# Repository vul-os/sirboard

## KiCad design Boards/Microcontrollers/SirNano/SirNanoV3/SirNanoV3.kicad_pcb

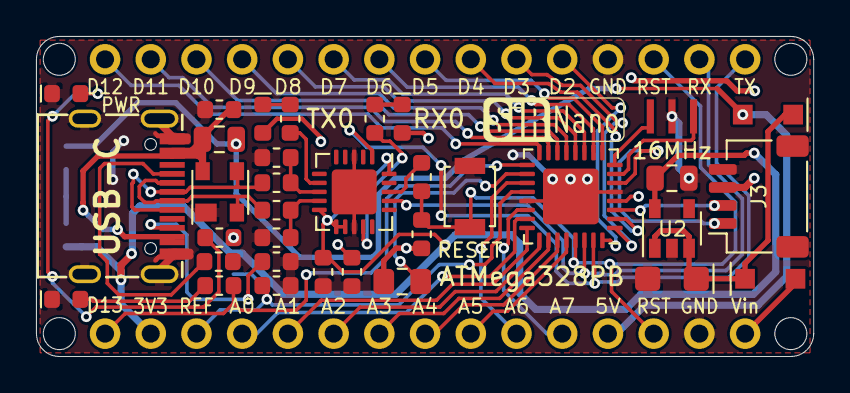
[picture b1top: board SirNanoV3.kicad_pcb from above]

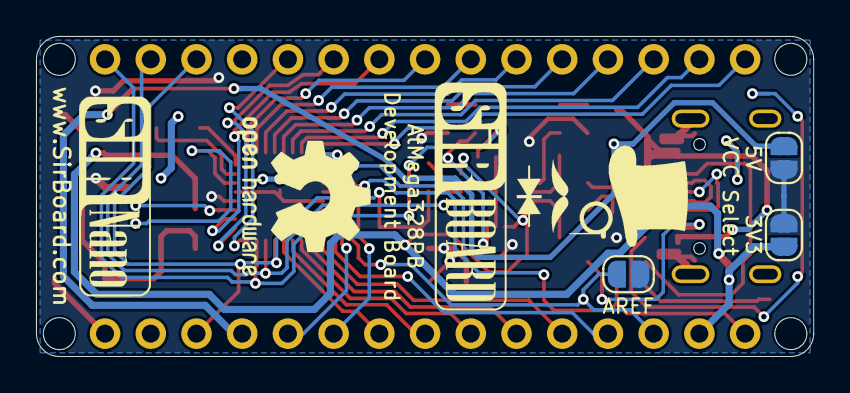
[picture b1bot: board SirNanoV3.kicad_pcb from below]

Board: 2 copper layers, 43.2 x 17.8 mm, 43 parts (5 on the bottom side), 49 nets.

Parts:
C1, C3, C9, C11: 100nF; C_0603_1608Metric
C2, C4: 47pF; C_0603_1608Metric
C6: 10nF; C_0603_1608Metric
C7: 10uF; C_0805_2012Metric
C8: 22uF; CP_EIA-3216-12_Kemet-S
D1: PRTR5V0U2X; SOT-143
D2, D3: MBR120; D_SOD-123F
D13: LED; LED_0603_1608Metric
F1: 500mA; R_0805_2012Metric
H1, H2, H3, H4: MountingHole; MountingHole_2.2mm_M2
J1, J2: Conn_01x15; PinHeader_1x15_P2.54mm_Vertical
J3: SirBlue; SirBlue_Connector
JP1, JP2, JP3: AREF; SolderJumper-2_P1.3mm_Open_RoundedPad1.0x1.5mm
L1: 10uH; L_0805_2012Metric_Pad1.15x1.40mm_HandSolder
PWR: LED; LED_0603_1608Metric
R1, R2: 27e; R_0603_1608Metric
R3: 10k; R_0603_1608Metric
R4, R8, R9, R10: 1k; R_0603_1608Metric
R11, R12: 5K1; R_0603_1608Metric
RESET: SW_Push; SW_SPST_B3U-1000P
RX0: LED; LED_0603_1608Metric
TX0: LED; LED_0603_1608Metric
U1: ATmega328PB-MU; QFN-32-1EP_5x5mm_P0.5mm_EP3.1x3.1mm
U2: SPX3819M5-L-3-3; SOT-23-5
U3: FT231XQ; QFN-20-1EP_4x4mm_P0.5mm_EP2.5x2.5mm
USB-C: USB_C_Plug_USB2.0; USB_C
Y1: 16MHz; Resonator_SMD_muRata_CSTxExxV-3Pin_3.0x1.1mm

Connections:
3V3: C3.1, C7.1, J2.14, JP3.1, U2.5, U3.10, U3.11, U3.12, U3.20
/D13LED: D13.2, R9.2
/LDO_in: C8.1, D2.1, D3.1, U2.1, U2.3
/PWRLED: PWR.2, R10.2
/RXLED: R4.2, RX0.1
/TXLED: R8.2, TX0.1
/X1: U1.7, Y1.3
/X2: U1.8, Y1.1
/uD+: C2.1, R1.2, U3.8
/uD-: C4.1, R2.2, U3.9
A0: J2.12, U1.23
A1: J2.11, U1.24
A2: J2.10, U1.25
A3: J2.9, U1.26
A4: J2.8, U1.27
A5: J2.7, U1.28
A6: J2.6, U1.19
A7: J2.5, U1.22
AREF: C1.1, J2.13, JP1.1, U1.20
D2: J1.11, U1.32
D3: J1.10, U1.1
D4: J1.9, U1.2
D5: J1.8, U1.9
D6: J1.7, U1.10
D7: J1.6, U1.11
D8: J1.5, U1.12
D9: J1.4, U1.13
D10: J1.3, U1.14
D11: J1.2, U1.15
D12: J1.1, U1.16
D13: J2.15, R9.1, U1.17
D+: D1.3, R1.1, USB-C.A6, USB-C.B6
D-: D1.2, R2.1, USB-C.A7, USB-C.B7
GND: C1.2, C2.2, C3.2, C4.2, C6.2, C7.2, C8.2, C9.2, D1.1, D13.1, J1.12, J2.2, J3.4, PWR.1, R11.1, R12.1, RESET.2, U1.5, U1.21, U1.33, U2.2, U3.3, U3.13, U3.21, USB-C.A1, USB-C.A12, USB-C.B1, USB-C.B12, USB-C.S1, Y1.2
unnamed: C11.2, U3.18
unnamed: L1.2, U1.18
unnamed: R12.2, USB-C.A5
unnamed: R11.2, USB-C.B5
RESET: C11.1, J1.13, J2.3, R3.2, RESET.1, U1.29
RX: J1.14, U1.30, U3.17
RX_LED: R4.1, U3.14
SCL1: J3.1, U1.6
SDA1: J3.2, U1.3
TX: J1.15, U1.31, U3.1
TX_LED: R8.1, U3.7
VBUS: C6.1, D1.4, F1.2, USB-C.A4, USB-C.A9, USB-C.B4, USB-C.B9
VCC: C9.1, J3.3, JP1.2, JP2.2, JP3.2, L1.1, R3.1, R10.1, RX0.2, TX0.2, U1.4
VIN: D3.2, J2.1
VUSB: D2.2, F1.1, J2.4, JP2.1

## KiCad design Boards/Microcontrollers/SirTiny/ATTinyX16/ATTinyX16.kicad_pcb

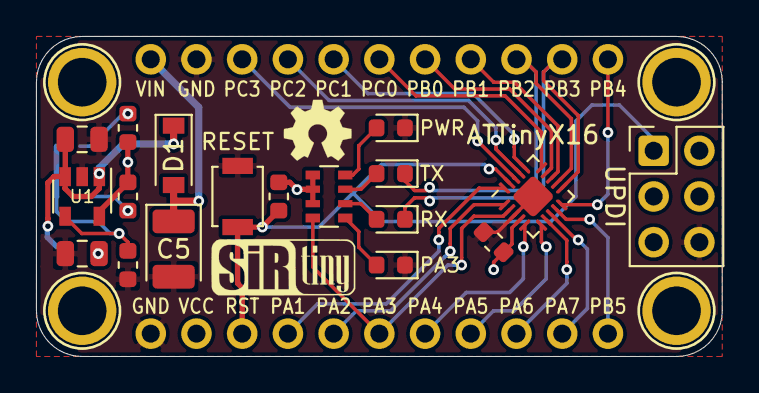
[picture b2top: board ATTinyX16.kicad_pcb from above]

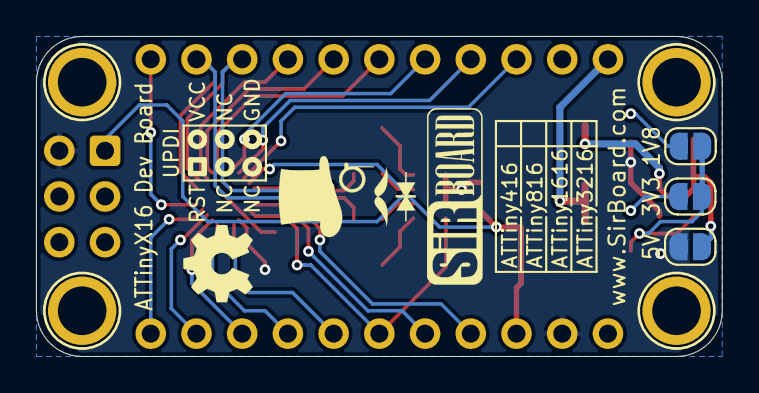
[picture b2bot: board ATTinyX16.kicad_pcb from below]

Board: 2 copper layers, 38.1 x 17.8 mm, 27 parts (5 on the bottom side), 29 nets.

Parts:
1V8, 3V3, 5V: SolderJumper_2_Open; SolderJumper-2_P1.3mm_Open_RoundedPad1.0x1.5mm
C1: 10uF; C_0805_2012Metric
C2: 2u2; C_0805_2012Metric
C3: 100nF; C_0603_1608Metric
C5: 22uF; CP_EIA-3528-15_AVX-H
D1: MBR120; D_SOD-123
H1, H2, H3, H4: MountingHole; MountingHole_M2.5_SirBoard
J1, J2: Conn_01x11; PinHeader_1x11_P2.54mm_Vertical
PA3: BLUE; LED_0603_1608Metric
PWR: RED; LED_0603_1608Metric
R3: 39k; R_0603_1608Metric
R4: 12.4k; R_0603_1608Metric
R5: 18k; R_0603_1608Metric
R6: 10k; R_0603_1608Metric
RESET: RST; SW_SPST_B3U-1000P
RN1: 330E; R_Array_Convex_4x0603
RX: YEL; LED_0603_1608Metric
TX: YEL; LED_0603_1608Metric
U1: AP7365; SOT-23-5
U2: ATtiny1616-M; VQFN-20-1EP_3x3mm_P0.4mm_EP1.7x1.7mm
UPDI: UPDI; PinHeader_2x03_P2.54mm_Vertical

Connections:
/1V8: 1V8.2, R5.2
/3V3: 3V3.2, R3.2
/ADJ: 1V8.1, 3V3.1, R4.1, U1.4
GND: C1.2, C2.2, C3.2, C5.2, J1.1, J2.2, PA3.1, PWR.1, R4.2, RESET.2, U1.2, U2.3, U2.21, UPDI.6
unnamed: 5V.2, C1.1, D1.1, U1.1, U1.3
unnamed: PA3.2, RN1.1
unnamed: PWR.2, RN1.4
unnamed: RN1.2, RX.2
unnamed: RN1.3, TX.2
PA1: J1.4, U2.20
PA2: J1.5, U2.1
PA3: J1.6, RN1.8, U2.2
PA4: J1.7, U2.5
PA5: J1.8, U2.6
PA6: J1.9, U2.7
PA7: J1.10, U2.8
PB0: J2.7, U2.14
PB1: J2.8, U2.13
PB4: J2.11, U2.10
PB5: J1.11, U2.9
PC0: J2.6, U2.15
PC1: J2.5, U2.16
PC2: J2.4, U2.17
PC3: J2.3, U2.18
RST: J1.3, R6.2, RESET.1, U2.19, UPDI.1
RXD: J2.10, RX.1, U2.11
TXD: J2.9, TX.1, U2.12
VCC: 5V.1, C2.1, C3.1, J1.2, R3.1, R5.1, R6.1, RN1.5, RN1.6, RN1.7, U1.5, U2.4, UPDI.2
VIN: C5.1, D1.2, J2.1

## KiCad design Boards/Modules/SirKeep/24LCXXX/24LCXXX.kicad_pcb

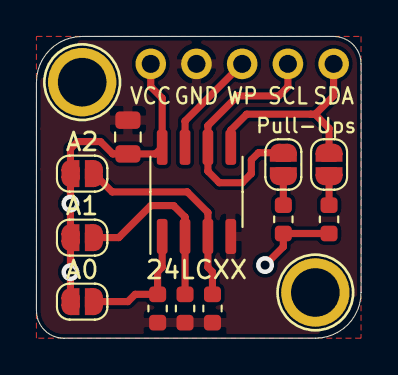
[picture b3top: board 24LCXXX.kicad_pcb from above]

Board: 2 copper layers, 18.0 x 16.8 mm, 15 parts (0 on the bottom side), 10 nets.

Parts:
24LCXX: 24LC1025; SOIC-8_3.9x4.9mm_P1.27mm
A0, A1, A2: SolderJumper_2_Open; SolderJumper-2_P1.3mm_Open_RoundedPad1.0x1.5mm
C1: 1uF; C_0805_2012Metric
H1, H2: MountingHole; MountingHole_M2.5_SirBoard
J1: Conn_01x05; PinHeader_1x05_P2.54mm_Vertical
R1, R2: 4K7; R_0603_1608Metric
R3, R4, R5: 10K; R_0603_1608Metric
SCL: SolderJumper_2_Open; SolderJumper-2_P1.3mm_Open_RoundedPad1.0x1.5mm
SDA: SolderJumper_2_Open; SolderJumper-2_P1.3mm_Open_RoundedPad1.0x1.5mm

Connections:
/A0: 24LCXX.1, A0.1, R3.1
/A1: 24LCXX.2, A1.1, R4.1
/A2: 24LCXX.3, A2.1, R5.1
GND: 24LCXX.4, C1.2, J1.2, R3.2, R4.2, R5.2
unnamed: R1.1, SCL.2
unnamed: R2.1, SDA.2
SCL: 24LCXX.6, J1.4, SCL.1
SDA: 24LCXX.5, J1.5, SDA.1
VCC: 24LCXX.8, A0.2, A1.2, A2.2, C1.1, J1.1, R1.2, R2.2
WP: 24LCXX.7, J1.3

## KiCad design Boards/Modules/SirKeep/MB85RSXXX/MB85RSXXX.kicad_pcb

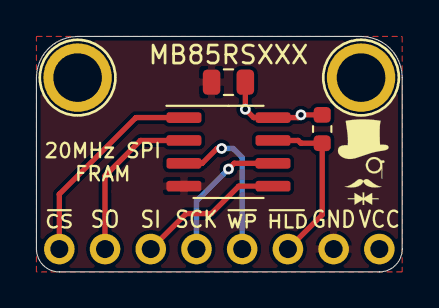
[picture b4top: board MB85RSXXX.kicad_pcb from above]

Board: 2 copper layers, 20.3 x 13.1 mm, 6 parts (1 on the bottom side), 8 nets.

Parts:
C1: 10uF; C_0805_2012Metric
H1, H2: MountingHole; MountingHole_M2.5_SirBoard
J1: Conn_01x08; PinHeader_1x08_P2.54mm_Vertical
MB85RSXXX: MB85RS64; SOIC-8_3.9x4.9mm_P1.27mm
R3: 10K; R_0603_1608Metric

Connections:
CS: J1.1, MB85RSXXX.1
GND: C1.2, J1.7, MB85RSXXX.4
HOLD: J1.6, MB85RSXXX.7, R3.2
SCK: J1.4, MB85RSXXX.6
SI: J1.3, MB85RSXXX.5
SO: J1.2, MB85RSXXX.2
VCC: C1.1, J1.8, MB85RSXXX.8, R3.1
WP: J1.5, MB85RSXXX.3

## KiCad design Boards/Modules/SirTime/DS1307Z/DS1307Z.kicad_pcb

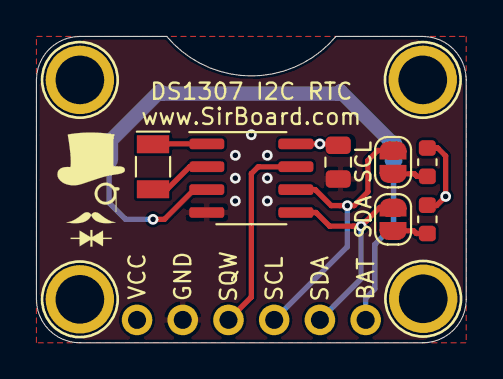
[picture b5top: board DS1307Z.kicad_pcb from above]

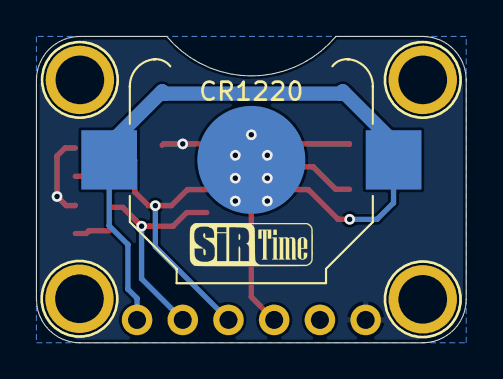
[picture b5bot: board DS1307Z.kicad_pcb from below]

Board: 2 copper layers, 23.9 x 17.0 mm, 13 parts (2 on the bottom side), 10 nets.

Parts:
C1: 1uF; C_0805_2012Metric
CR1220: Battery_Cell; BatteryHolder_Keystone_3000_1x12mm
H1, H2, H3, H4: MountingHole; MountingHole_M2.5_SirBoard
J1: Conn_01x06; PinHeader_1x06_P2.54mm_Vertical
R1, R2: 4K7; R_0603_1608Metric
SCL: SolderJumper_2_Open; SolderJumper-2_P1.3mm_Open_RoundedPad1.0x1.5mm
SDA: SolderJumper_2_Open; SolderJumper-2_P1.3mm_Open_RoundedPad1.0x1.5mm
U1: DS1307ZN+; SOIC-8_3.9x4.9mm_P1.27mm
Y1: SMD31327681252090; Crystal_SMD_EuroQuartz_EQ161-2Pin_3.2x1.5mm

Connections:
GND: C1.2, CR1220.2, J1.5, U1.4
unnamed: R1.1, SDA.2
unnamed: R2.1, SCL.2
unnamed: U1.1, Y1.1
unnamed: U1.2, Y1.2
SCL: J1.3, SCL.1, U1.6
SDA: J1.2, SDA.1, U1.5
SQW: J1.4, U1.7
VBAT: CR1220.1, J1.1, U1.3
VCC: C1.1, J1.6, R1.2, R2.2, U1.8

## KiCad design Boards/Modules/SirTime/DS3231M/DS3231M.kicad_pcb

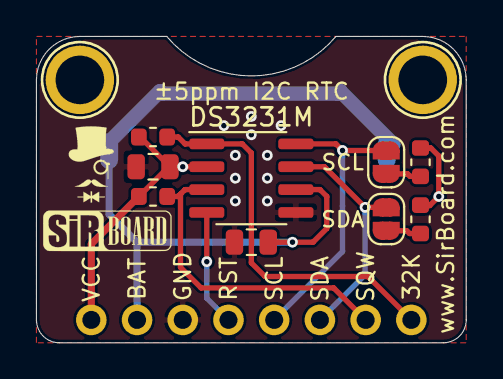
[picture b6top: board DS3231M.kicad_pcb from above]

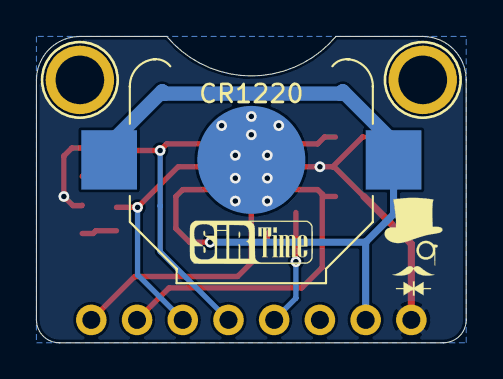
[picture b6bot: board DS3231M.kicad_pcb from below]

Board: 2 copper layers, 23.9 x 17.0 mm, 13 parts (2 on the bottom side), 10 nets.

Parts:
C1, C2: 1uF; C_0805_2012Metric
CR1220: Battery_Cell; BatteryHolder_Keystone_3000_1x12mm
DS3231M: DS3231MZ; SOIC-8_3.9x4.9mm_P1.27mm
H1, H2: MountingHole; MountingHole_M2.5_SirBoard
J3: Conn_01x08; PinHeader_1x08_P2.54mm_Vertical
R1, R2: 4K7; R_0603_1608Metric
R3, R4: 10K; R_0603_1608Metric
SCL: SolderJumper_2_Open; SolderJumper-2_P1.3mm_Open_RoundedPad1.0x1.5mm
SDA: SolderJumper_2_Open; SolderJumper-2_P1.3mm_Open_RoundedPad1.0x1.5mm

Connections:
32K: DS3231M.1, J3.8, R3.1
GND: C1.2, C2.2, CR1220.2, DS3231M.5, J3.3
unnamed: R1.1, SDA.2
unnamed: R2.1, SCL.2
RST: DS3231M.4, J3.4
SCL: DS3231M.8, J3.5, SCL.1
SDA: DS3231M.7, J3.6, SDA.1
SQW: DS3231M.3, J3.7, R4.1
VBAT: C2.1, CR1220.1, DS3231M.6, J3.2
VCC: C1.1, DS3231M.2, J3.1, R1.2, R2.2, R3.2, R4.2

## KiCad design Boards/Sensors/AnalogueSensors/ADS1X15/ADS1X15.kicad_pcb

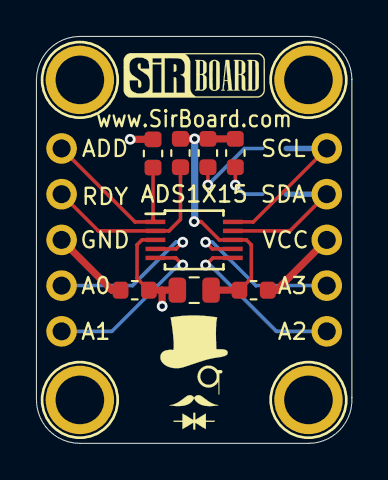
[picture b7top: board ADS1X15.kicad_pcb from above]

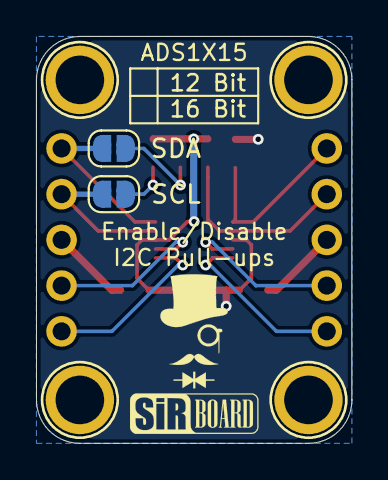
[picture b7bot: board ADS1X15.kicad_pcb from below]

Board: 2 copper layers, 17.5 x 22.6 mm, 16 parts (4 on the bottom side), 14 nets.

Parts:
ADS1X15: ADS1115IDGS; TSSOP-10_3x3mm_P0.5mm
C1: 1uF; C_0805_2012Metric
FB1, FB2: Ferrite_Bead; L_0603_1608Metric
H1, H2, H3, H4: MountingHole; MountingHole_M2.5_SirBoard
J1, J2: Conn_01x05; PinHeader_1x05_P2.54mm_Vertical
R1, R2, R3, R4: 10K; R_0603_1608Metric
SCL: SolderJumper_2_Open; SolderJumper-2_P1.3mm_Open_RoundedPad1.0x1.5mm
SDA: SolderJumper_2_Open; SolderJumper-2_P1.3mm_Open_RoundedPad1.0x1.5mm

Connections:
ADD: ADS1X15.1, J1.1, R4.1
AIN0: ADS1X15.4, J1.4
AIN1: ADS1X15.5, J1.5
AIN2: ADS1X15.6, J2.5
AIN3: ADS1X15.7, J2.4
ALERT: ADS1X15.2, J1.2, R3.1
GND: FB1.1, J1.3
GND_B: ADS1X15.3, C1.2, FB1.2, R4.2
unnamed: R1.1, SCL.2
unnamed: R2.1, SDA.2
SCL: ADS1X15.10, J2.1, SDA.1
SDA: ADS1X15.9, J2.2, SCL.1
VCC: FB2.1, J2.3
VCC_B: ADS1X15.8, C1.1, FB2.2, R1.2, R2.2, R3.2
